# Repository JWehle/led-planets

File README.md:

# led-planets
A small controller board for some an LED lit planet decoration of mine.

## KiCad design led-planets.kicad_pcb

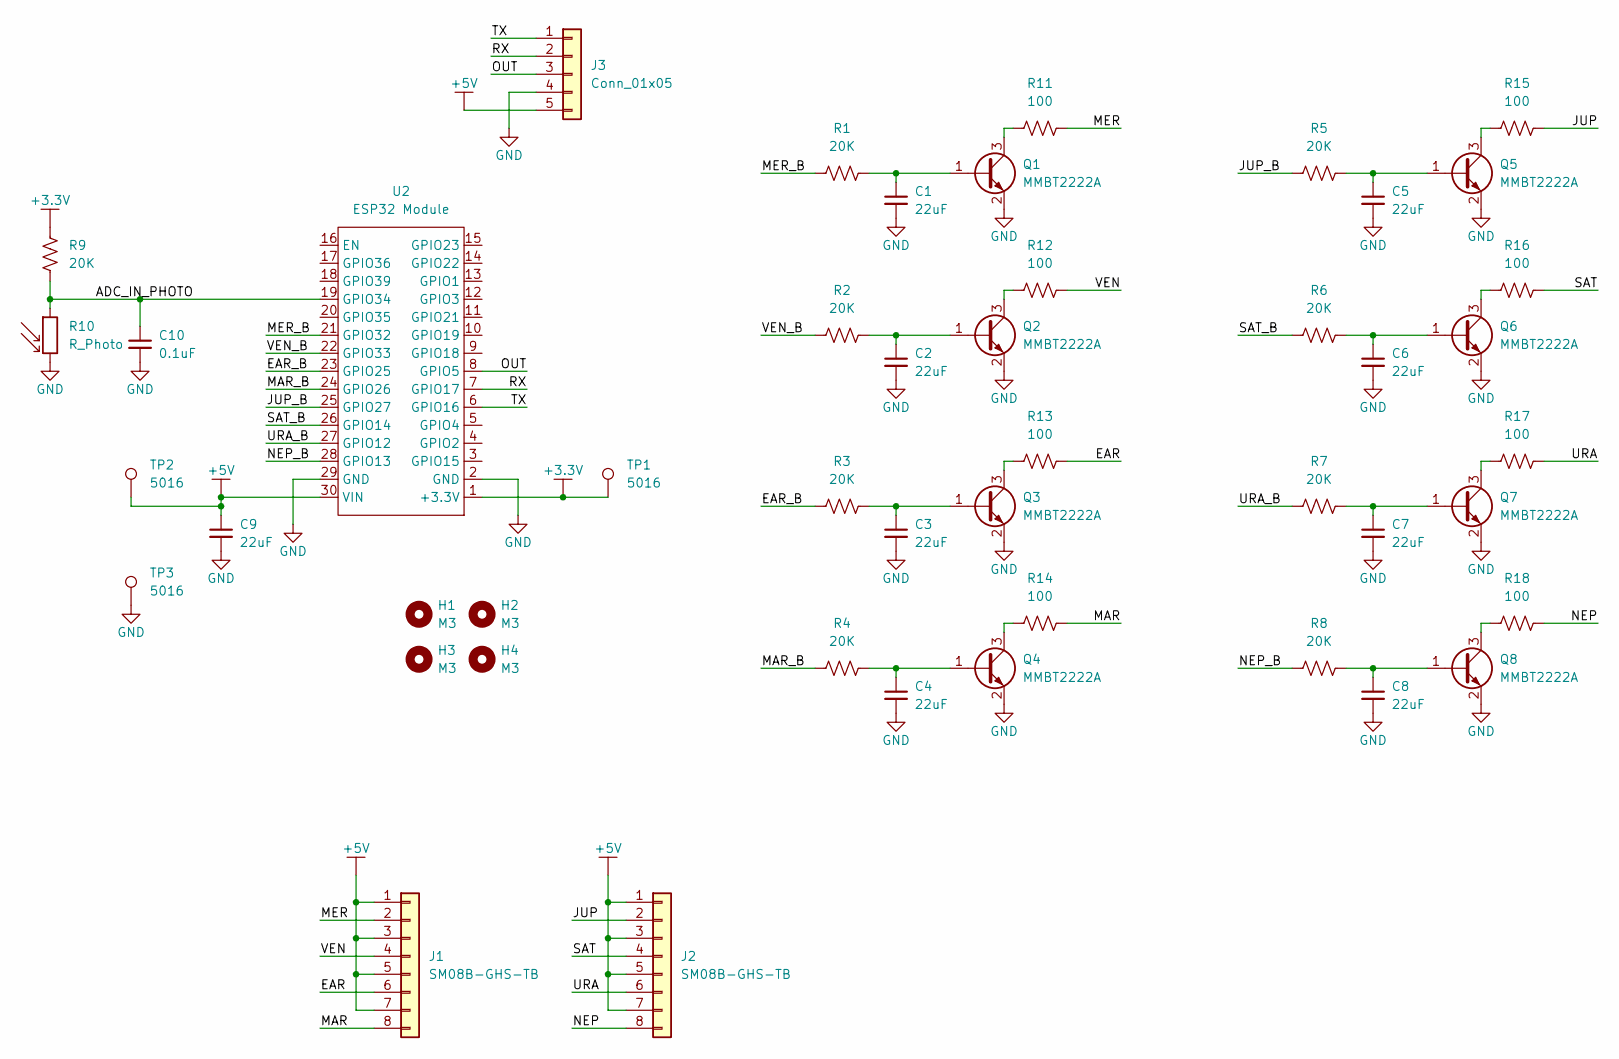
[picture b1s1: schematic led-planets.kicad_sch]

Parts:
C1, C2, C3, C4, C5, C6, C7, C8, C9: 22uF; C_0603_1608Metric_Pad1.08x0.95mm_HandSolder
C10: 0.1uF; C_0603_1608Metric_Pad1.08x0.95mm_HandSolder
H1, H2, H3, H4: M3; MountingHole_3.2mm_M3
J1, J2: SM08B-GHS-TB; JST_GH_SM08B-GHS-TB_1x08-1MP_P1.25mm_Horizontal
J3: Conn_01x05; PinSocket_1x05_P2.54mm_Vertical
Q1, Q2, Q3, Q4, Q5, Q6, Q7, Q8: MMBT2222A; SOT-23
R1, R2, R3, R4, R5, R6, R7, R8, R9: 20K; R_0603_1608Metric_Pad0.98x0.95mm_HandSolder
R10: R_Photo; R_LDR_5.0x4.1mm_P3mm_Vertical
R11, R12, R13, R14, R15, R16, R17, R18: 100; R_0603_1608Metric_Pad0.98x0.95mm_HandSolder
TP1, TP2, TP3: 5016; TestPoint_Keystone_5016_Compact
U2: ESP32 Module; ESP32_MODULE

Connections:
+3.3V: R9.2, TP1.1, U2.1 (+3.3V)
+5V: C9.1, J1.1, J1.3, J1.5, J1.7, J2.1, J2.3, J2.5, J2.7, J3.5, TP2.1, U2.30 (VIN)
/ADC_IN_PHOTO: C10.1, R9.1, R10.1, U2.19 (GPIO34)
/EAR: J1.6, R13.2
/EAR_B: R3.1, U2.23 (GPIO25)
/JUP: J2.2, R15.2
/JUP_B: R5.1, U2.25 (GPIO27)
/MAR: J1.8, R14.2
/MAR_B: R4.1, U2.24 (GPIO26)
/MER: J1.2, R11.2
/MER_B: R1.1, U2.21 (GPIO32)
/NEP: J2.8, R18.2
/NEP_B: R8.1, U2.28 (GPIO13)
/OUT: J3.3, U2.8 (GPIO5)
/RX: J3.2, U2.7 (GPIO17)
/SAT: J2.4, R16.2
/SAT_B: R6.1, U2.26 (GPIO14)
/TX: J3.1, U2.6 (GPIO16)
/URA: J2.6, R17.2
/URA_B: R7.1, U2.27 (GPIO12)
/VEN: J1.4, R12.2
/VEN_B: R2.1, U2.22 (GPIO33)
GND: C1.2, C2.2, C3.2, C4.2, C5.2, C6.2, C7.2, C8.2, C9.2, C10.2, J3.4, Q1.2 (E), Q2.2 (E), Q3.2 (E), Q4.2 (E), Q5.2 (E), Q6.2 (E), Q7.2 (E), Q8.2 (E), R10.2, TP3.1, U2.2 (GND), U2.29 (GND)
unnamed: C1.1, Q1.1 (B), R1.2
unnamed: Q1.3 (C), R11.1
unnamed: C2.1, Q2.1 (B), R2.2
unnamed: Q2.3 (C), R12.1
unnamed: C3.1, Q3.1 (B), R3.2
unnamed: Q3.3 (C), R13.1
unnamed: C4.1, Q4.1 (B), R4.2
unnamed: Q4.3 (C), R14.1
unnamed: C5.1, Q5.1 (B), R5.2
unnamed: Q5.3 (C), R15.1
unnamed: C6.1, Q6.1 (B), R6.2
unnamed: Q6.3 (C), R16.1
unnamed: C7.1, Q7.1 (B), R7.2
unnamed: Q7.3 (C), R17.1
unnamed: C8.1, Q8.1 (B), R8.2
unnamed: Q8.3 (C), R18.1

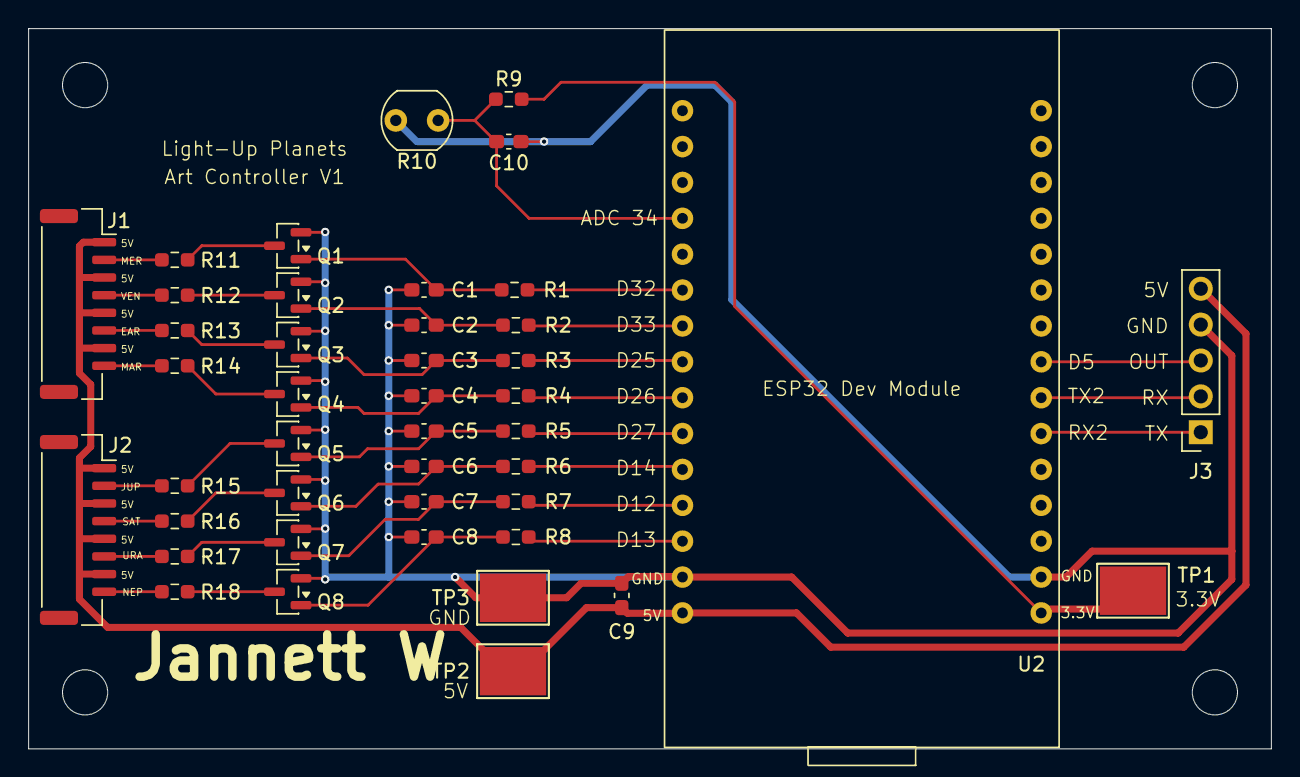
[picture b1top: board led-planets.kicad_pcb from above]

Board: 2 copper layers, 88.0 x 51.0 mm, 47 parts (0 on the bottom side), 39 nets.

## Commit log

2026-01-08 initial release
    added kicad project files
2026-01-08 starting schematic
2026-01-08 schematic changes
2026-01-28 layout and sch
2026-02-09 schematic
2026-02-09 schematic finished
2026-02-09 layout
2026-02-09 gerbers
